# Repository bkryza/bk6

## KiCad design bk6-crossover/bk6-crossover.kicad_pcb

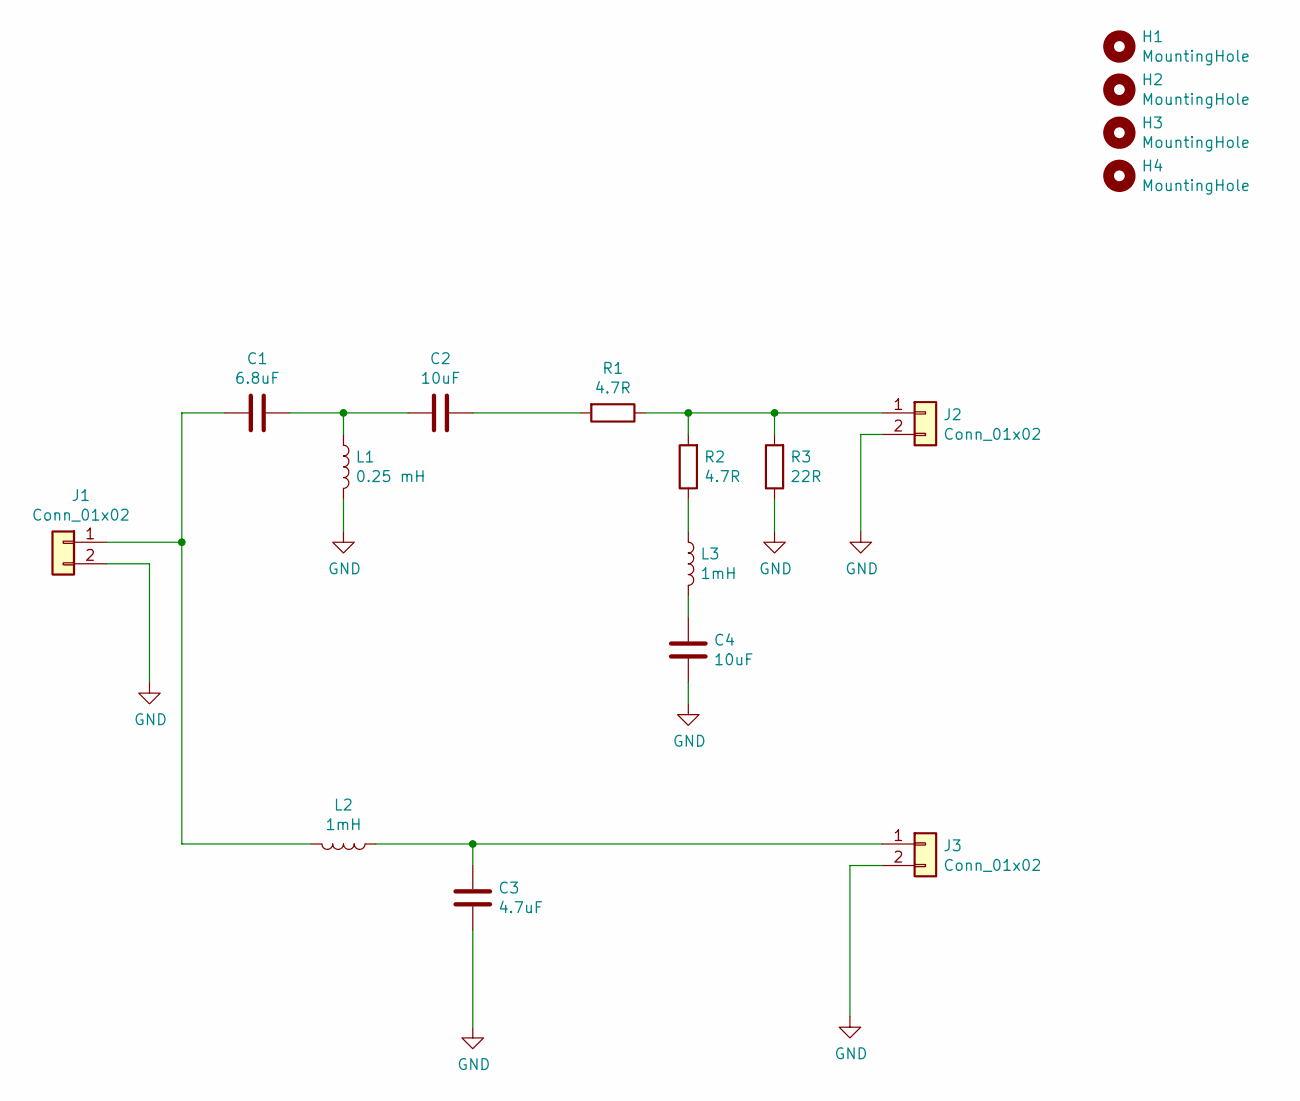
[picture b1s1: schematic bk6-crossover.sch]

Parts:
C1: 6.8uF; CP_Axial_L30.0mm_D18.0mm_P35.00mm_Horizontal
C2, C4: 10uF; CP_Axial_L30.0mm_D18.0mm_P35.00mm_Horizontal
C3: 4.7uF; CP_Axial_L30.0mm_D18.0mm_P35.00mm_Horizontal
H1, H2, H3, H4: MountingHole; MountingHole_3.2mm_M3
J1, J2, J3: Conn_01x02; AK505_2PIN
L1: 0.25 mH; L_Toroid_Horizontal_D35.1mm_P31.00mm_Vishay_TJ6
L2, L3: 1mH; L_Toroid_Horizontal_D35.1mm_P31.00mm_Vishay_TJ6
R1, R2: 4.7R; R_Axial_Power_L50.0mm_W9.0mm_P60.96mm
R3: 22R; R_Axial_Power_L50.0mm_W9.0mm_P60.96mm

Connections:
GND: C3.2, C4.1, J1.2, J2.2, J3.2, L1.2, R3.1
unnamed: C1.1, C2.2, L1.1
unnamed: C1.2, J1.1, L2.2
unnamed: C2.1, R1.2
unnamed: C3.1, J3.1, L2.1
unnamed: C4.2, L3.2
unnamed: J2.1, R1.1, R2.2, R3.2
unnamed: L3.1, R2.1

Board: 2 copper layers, 17 parts (0 on the bottom side), 8 nets, no tracks yet.

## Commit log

2020-10-17 Inital commit
